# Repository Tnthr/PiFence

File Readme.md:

# About PiFence

An arduino script and a shell script for use as a fence agent on a custom built power supply for a five node raspberry pi cluster.

The shell script is a fence agent designed to be used with pacemaker in a HA environment. 
The Arduino program is for an Arduino with ethernet shield connected to five seperate relays that operate five USB power supplies. This setup allows the Arduino to function as a STONITH device for a five node Raspberry Pi cluster.

The whole project is pretty rough but it works well enough for "production" use. Plenty of room for improvement though.
Recently added the first revision of a custom PCB. All of the files are from KiCAD. I do not recommend using this PCB design as is because it is extremely simple and only uses various breakout boards. The next version will be a real PCB that includes all of the discrete components. 

The project is designed to fit into a Raspberry Pi cluster case to be self-contained. Link to the case used is below.
https://www.printables.com/en/model/182055-raspberry-pi-4-cluster-case

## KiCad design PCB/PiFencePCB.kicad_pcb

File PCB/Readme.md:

# About PiFence PCB

The fence device is custom-made hardware that is run by the firmware in this repository. This PCB folder is the hardware.

The core of the hardware is an Arduino that controls five relays powering five USB ports. These ports provide power to each of five Raspberry Pi devices and the Arduino provides fencing capability. The Arduino has an ethernet port interface to provide external control.

The board has a power port for 18V input to supply the arduino and the five powered USB ports. 

Future plans include adding a USB C power input, two four-pin fan outputs, a 12V power output for the router, and integrating the ethernet port as well as converting the power outputs to USB C.

# Theory

The USB-C PD spec can deliver 20 volts and 5 amps which will provide up to 100 watts. This is plenty to power all of the board components. An alternate option is 15 volts at 3 amps. This will be just enough to power everything so long as there is not a high load on anything. Futher testing is probably required to ensure at least the initial bootup of all servers can be handled at the lower power level before providing support for it.

At the 20 volt input level power cannot be applied directly to the Arduino so a power step down will be required. A 12V step down will allow power to be applied to the arduino and to the router. A 5V step down with enough current output will be needed for the RPi power outputs and the fans.

Control of the fans should be provided by the Arduino. A temperature sensor will be added to the computer area of the case to provide input for controlling the speed of the fans.

# Component list

| Item          | Model              | Quantity |
| ------------- | ------------------ | -------- |
| MCU           | Arduino Nano Every | 1        |
| 12V Step down |                    | 1        |
| 5V Step down  |                    | ?        |
| Ethernet jack |                    | 1        |
| Relay         | PR13-5V-450-1C     | 5        |
| Temp sensor   |                    | 1        |
| USB C Port    |                    | 6        |

# Power requirements for all of the components

| Item    | Qty | Volt | Draw | Total  |
| ------- | --- | ---- | ---- | ------ |
| RPi4    | 5   | 5V   | 1.3A | 32.5W  |
| Fan     | 2   | 5V   | 0.2A | 2W     |
| Router  | 1   | 12V  | 1A   | 12W    |
| Arduino | 1   | 5V   | 25mA | 0.125W |

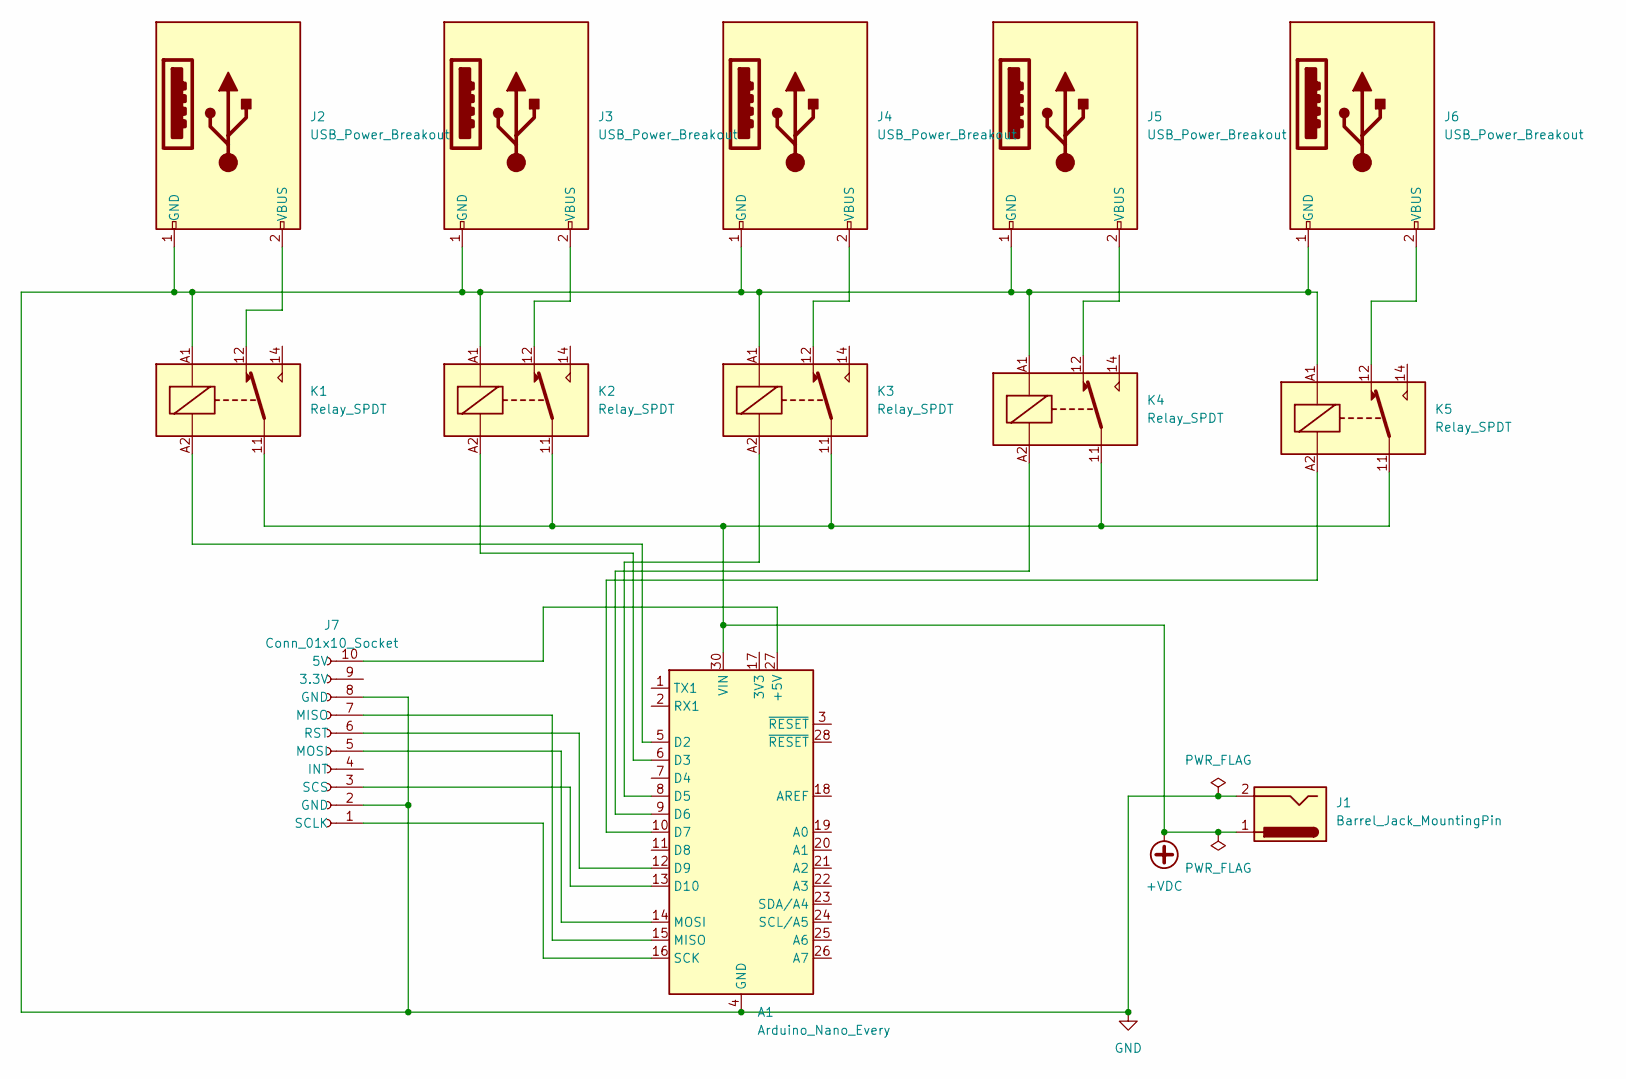
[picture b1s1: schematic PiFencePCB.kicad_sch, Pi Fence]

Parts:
A1: Arduino_Nano_Every; Arduino_Nano
J1: Barrel_Jack_MountingPin; BarrelJack_CUI_PJ-036AH-SMT_Horizontal
J2, J3, J4, J5, J6: USB_Power_Breakout; USB_Breakout_Board
J7: Conn_01x10_Socket; PinSocket_2x05_P2.54mm_Vertical
K1, K2, K3, K4, K5: Relay_SPDT; Relay_SPDT_Finder_36.11

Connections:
+VDC: A1.30 (VIN), J1.1, K1.11, K2.11, K3.11, K4.11, K5.11
GND: A1.4 (GND), A1.29 (GND), J1.2, J2.1 (GND), J3.1 (GND), J4.1 (GND), J5.1 (GND), J6.1 (GND), J7.2 (GND), J7.8 (GND), K1.A1, K2.A1, K3.A1, K4.A1, K5.A1
unnamed: A1.27 (+5V), J7.10 (5V)
unnamed: A1.5 (D2), K1.A2
unnamed: A1.6 (D3), K2.A2
unnamed: A1.8 (D5), K3.A2
unnamed: A1.9 (D6), K4.A2
unnamed: A1.10 (D7), K5.A2
unnamed: A1.12 (D9), J7.6 (RST)
unnamed: A1.13 (D10), J7.3 (SCS)
unnamed: A1.15 (MISO), J7.7 (MISO)
unnamed: A1.14 (MOSI), J7.5 (MOSI)
unnamed: A1.16 (SCK), J7.1 (SCLK)
unnamed: J2.2 (VBUS), K1.12
unnamed: J3.2 (VBUS), K2.12
unnamed: J4.2 (VBUS), K3.12
unnamed: J5.2 (VBUS), K4.12
unnamed: J6.2 (VBUS), K5.12

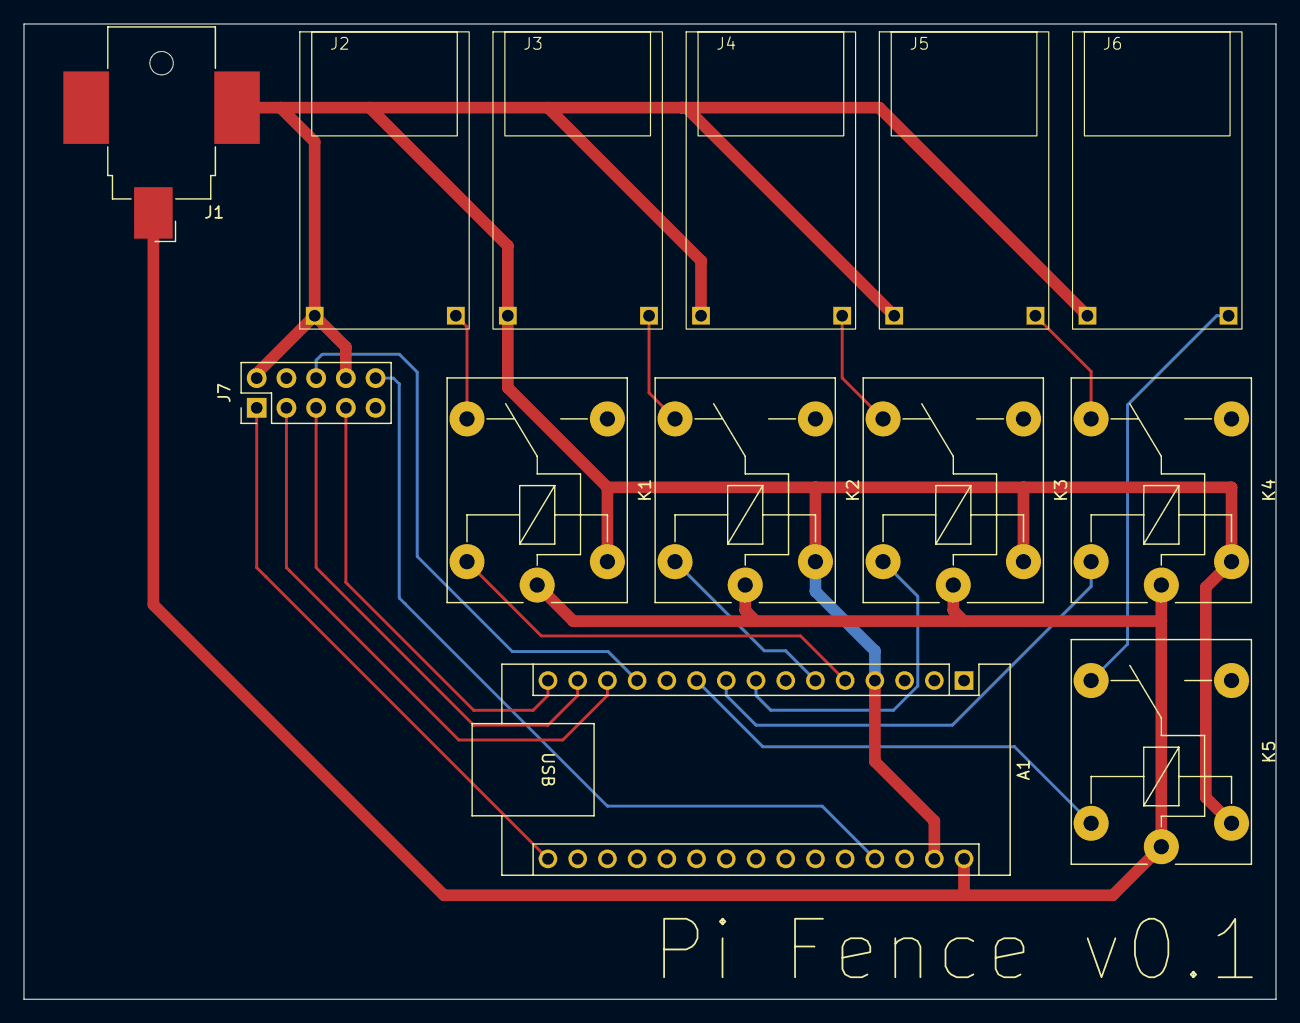
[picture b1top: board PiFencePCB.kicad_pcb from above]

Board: 2 copper layers, 107.0 x 83.3 mm, 13 parts (0 on the bottom side), 18 nets.

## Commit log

2022-08-04 changed to alternate version fence_ssh
2022-08-15 Added protocol doc
2022-08-15 complete change for template of arduino sketch
2022-08-15 first changes to the fence script
2022-08-16 minor changes
2022-08-18 variable name changes
2022-08-18 initial working version of the sketch
2022-08-19 Fully Functional Sketch!!
2022-08-22 chmod +x
2022-08-22 changed error reporting
2022-08-22 formatting changes
2022-08-23 fixed monitor function
2022-08-23 changed node names
2022-08-24 added gitignore
2022-08-24 changed monitor funtion to use ping
2022-08-26 major update to match what is actually happening
2022-10-20 changed required properties
2022-12-22 ready for testing with fan controls
2023-01-04 added config for VSCode Arduino
2023-01-04 changed mac addr, added debug code, cleaned up
2023-01-04 fixed a foolish buffer overflow
2023-01-07 Numerous changes throughout if ethernet fails retry changed debug to preprocessor statements added some debug outputs for port numbers shortened reboot delay
2023-06-19 fixed the metadata function and host naming
2023-09-14 Added testing MAC
2023-09-14 Added debug option to enable serial output
2023-09-19 Added PCB files
2023-09-23 Removed backup files
2023-09-23 dont commit with kicad still open
2023-09-23 changed back to production state
2023-09-23 Formatting and Line ending fixes
2023-09-24 Added a readme.md
2023-10-15 Update Readme.md
    added link to printable case.
2024-01-15 fixed invalid metadata
2024-01-27 Added a PCB readme. Some small changes to the schematic
